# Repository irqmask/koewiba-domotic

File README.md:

# koewiba-domotic
home-automation

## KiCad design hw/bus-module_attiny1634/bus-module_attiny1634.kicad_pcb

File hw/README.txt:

To load KICAD symbols and footprints, make a symbolic link called 'kicadlibrary' to your checked-out symbol- and footprint- library.
e.g. ln -s ~/Projekte/electronic/00library/kicad/ kicadlibrary

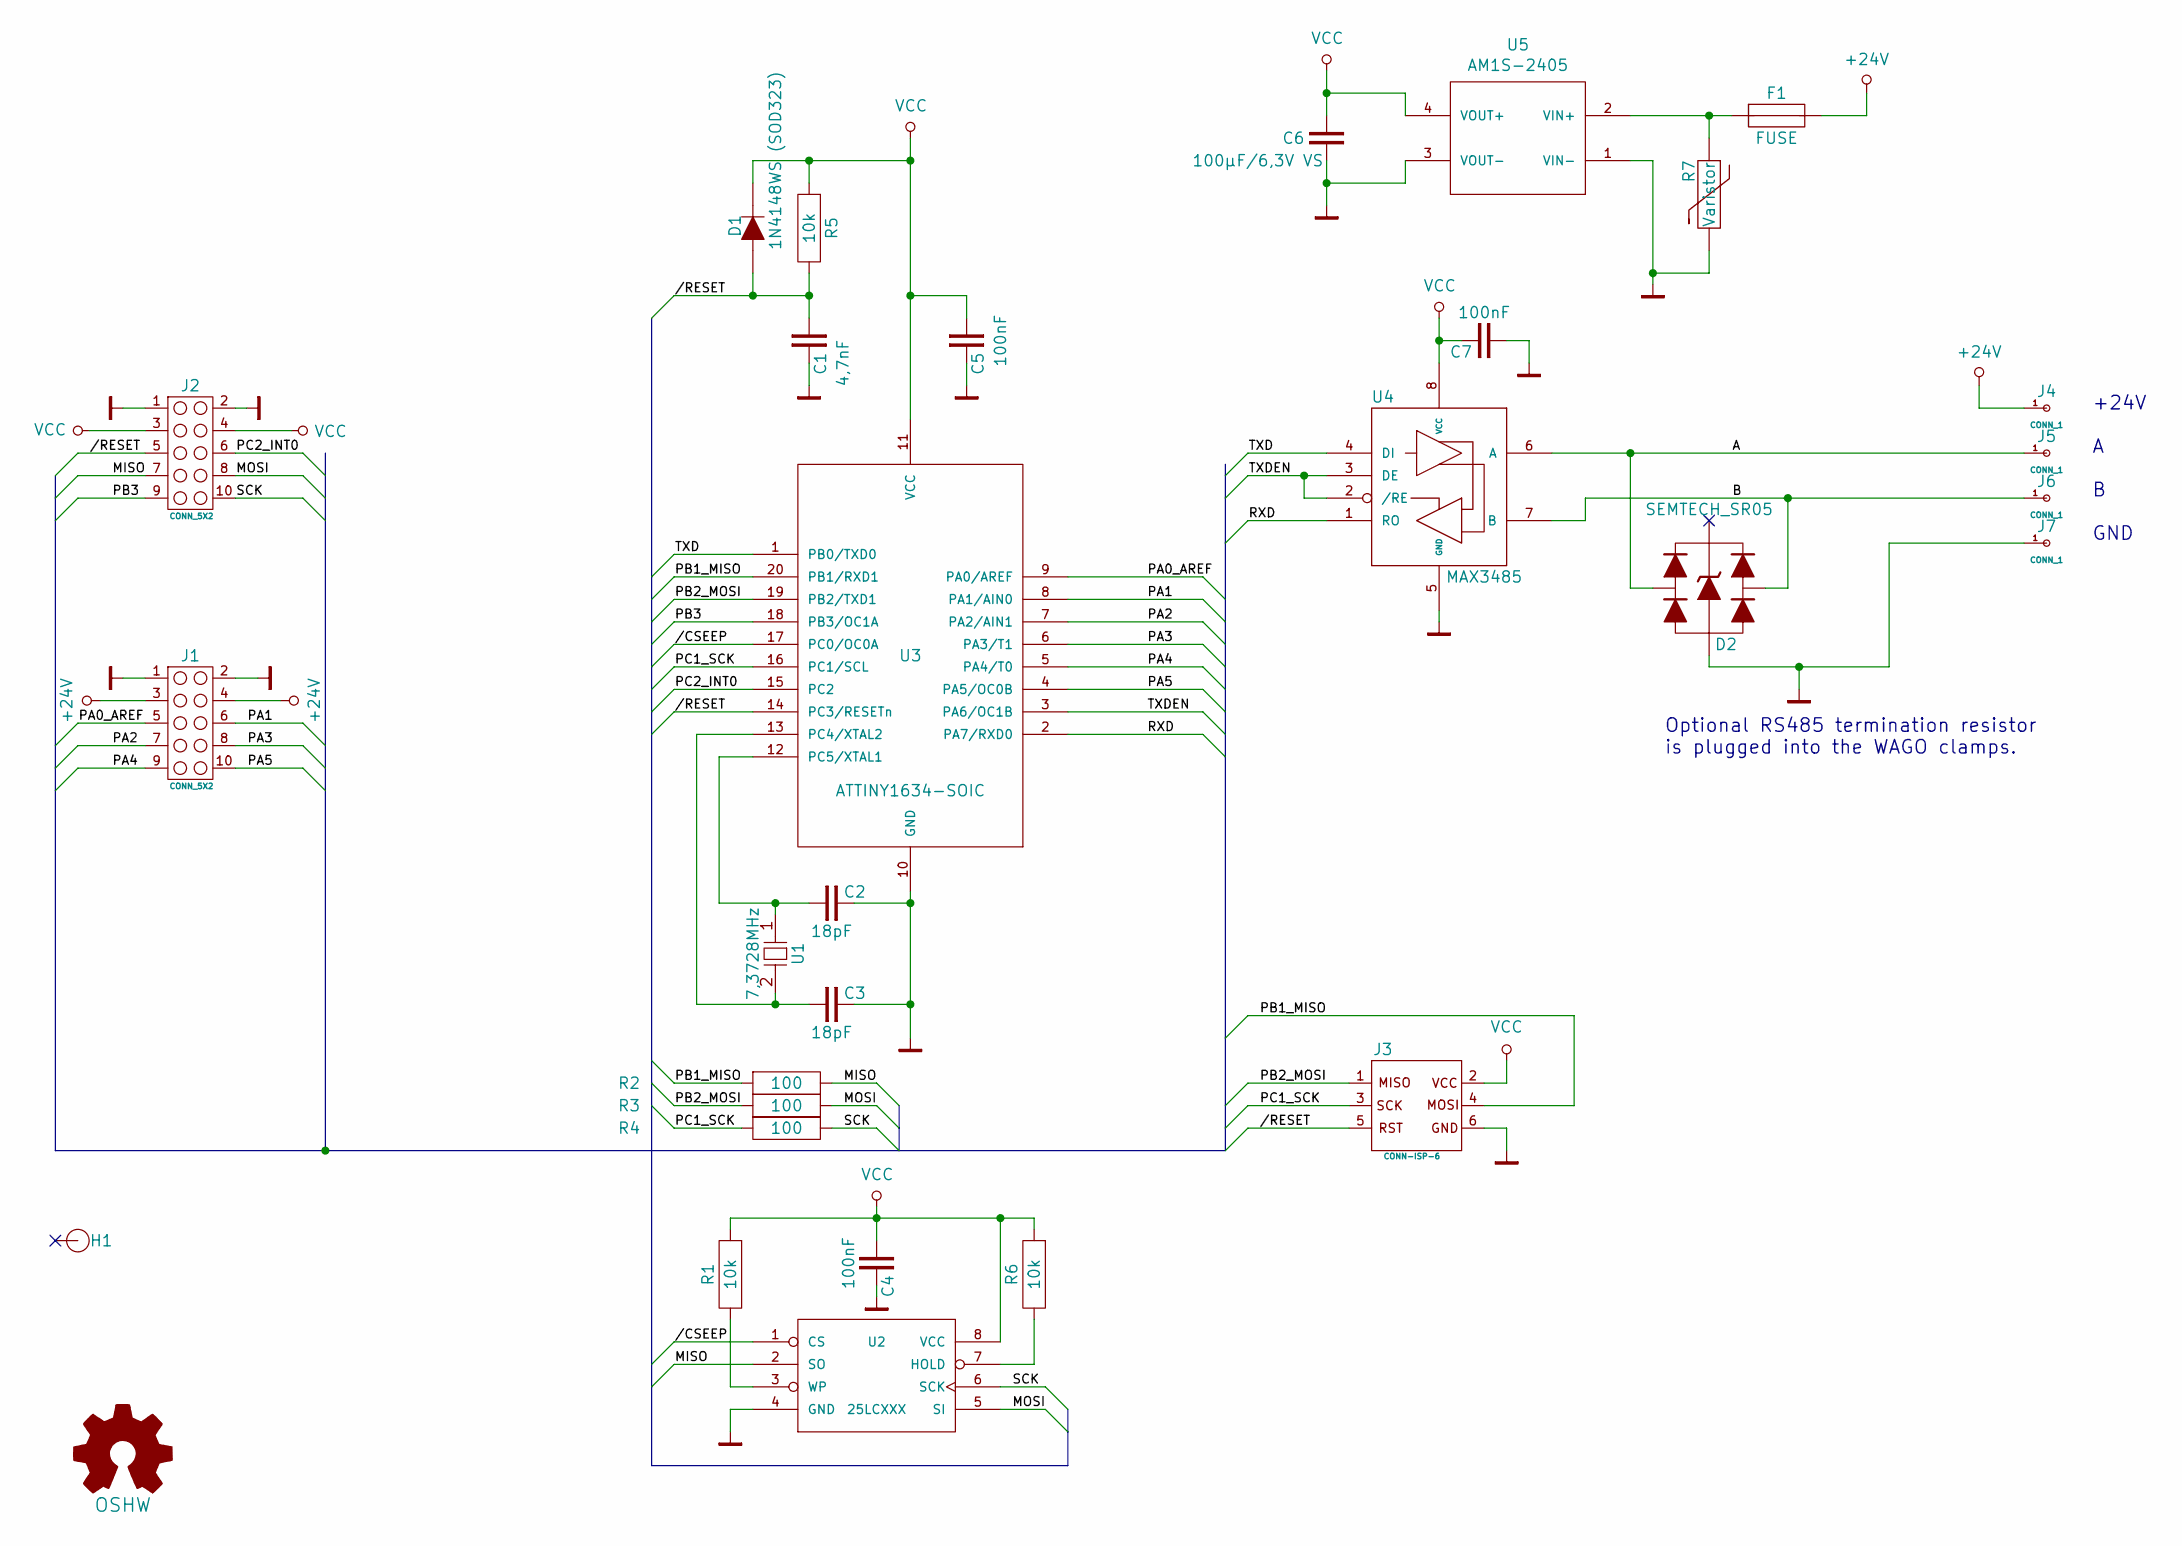
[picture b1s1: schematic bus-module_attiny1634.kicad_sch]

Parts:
C1: 4,7nF; C_0805
C2, C3: 18pF; C_0805
C4, C5, C7: 100nF; C_0805
C6: 100µF/6,3V VS; C_1206
D1: 1N4148WS (SOD323); D_SOD323
D2: SEMTECH_SR05; D_SOT143
F1: FUSE; R_1206
H1: HOLE; HOLE_2.5mm
J1, J2: CONN_5X2; HEADER_5x2
J3: CONN-ISP-6; HEADER_3x2
J4, J5, J6, J7: CONN_1; WAGO243
LOGO1: OSHW; Symbol_OSHW-Logo_SilkScreen
R1, R5, R6: 10k; R_0805
R2, R3, R4: 100; R_0805
R7: Varistor; R400
U1: 7,3728MHz; CRY_HC49_SMD
U2: 25LCXXX; SO8E
U3: ATTINY1634-SOIC; SO20L
U4: MAX3485; SO8E
U5: AM1S-2405; AM1S-XXXX_SIL4

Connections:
+24V: F1.2, J1.3, J1.4, J4.1
//CSEEP: U2.1 (CS), U3.17 (PC0/OC0A)
//RESET: C1.1, D1.1 (A), J2.5, J3.5, R5.2, U3.14 (PC3/RESETn)
/A: D2.4, J5.1, U4.6 (A)
/B: D2.3, J6.1, U4.7 (B)
/MISO: J2.7, R2.2, U2.2 (SO)
/MOSI: J2.8, R3.2, U2.5 (SI)
/PA0_AREF: J1.5, U3.9 (PA0/AREF)
/PA1: J1.6, U3.8 (PA1/AIN0)
/PA2: J1.7, U3.7 (PA2/AIN1)
/PA3: J1.8, U3.6 (PA3/T1)
/PA4: J1.9, U3.5 (PA4/T0)
/PA5: J1.10, U3.4 (PA5/OC0B)
/PB1_MISO: J3.4, R2.1, U3.20 (PB1/RXD1)
/PB2_MOSI: J3.1, R3.1, U3.19 (PB2/TXD1)
/PB3: J2.9, U3.18 (PB3/OC1A)
/PC1_SCK: J3.3, R4.1, U3.16 (PC1/SCL)
/PC2_INT0: J2.6, U3.15 (PC2)
/RXD: U3.2 (PA7/RXD0), U4.1 (RO)
/SCK: J2.10, R4.2, U2.6 (SCK)
/TXD: U3.1 (PB0/TXD0), U4.4 (DI)
/TXDEN: U3.3 (PA6/OC1B), U4.2 (/RE), U4.3 (DE)
GND: C1.2, C2.2, C3.2, C4.2, C5.2, C6.2, C7.1, D2.1, J1.1, J1.2, J2.1, J2.2, J3.6, J7.1, R7.2, U2.4 (GND), U3.10 (GND), U4.5 (GND), U5.1 (VIN-), U5.3 (VOUT-)
unnamed: C2.1, U1.1, U3.12 (PC5/XTAL1)
unnamed: C3.1, U1.2, U3.13 (PC4/XTAL2)
unnamed: F1.1, R7.1, U5.2 (VIN+)
unnamed: R1.2, U2.3 (WP)
unnamed: R6.2, U2.7 (HOLD)
VCC: C4.1, C5.1, C6.1, C7.2, D1.2 (C), J2.3, J2.4, J3.2, R1.1, R5.1, R6.1, U2.8 (VCC), U3.11 (VCC), U4.8 (VCC), U5.4 (VOUT+)

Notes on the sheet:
+24V A B GND
Optional RS485 termination resistor is plugged into the WAGO clamps.

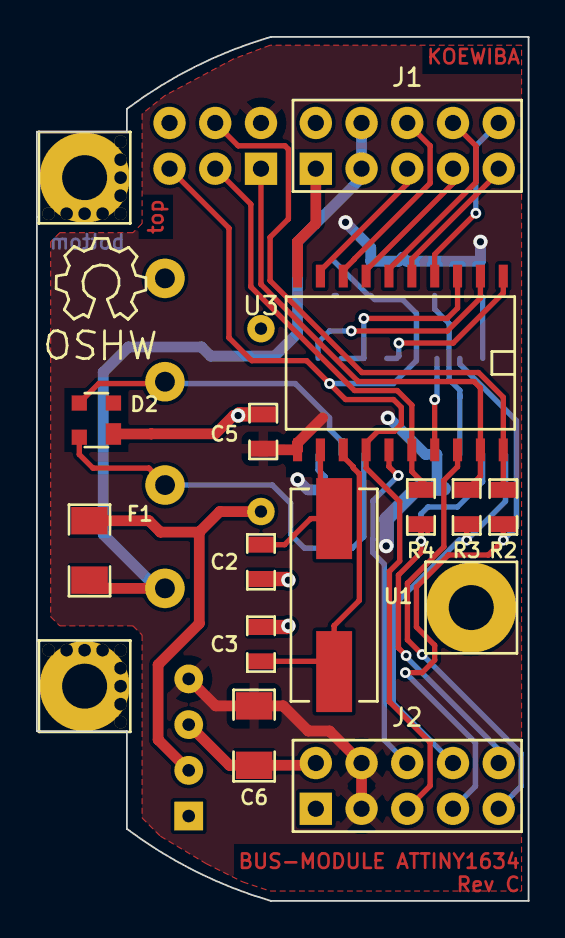
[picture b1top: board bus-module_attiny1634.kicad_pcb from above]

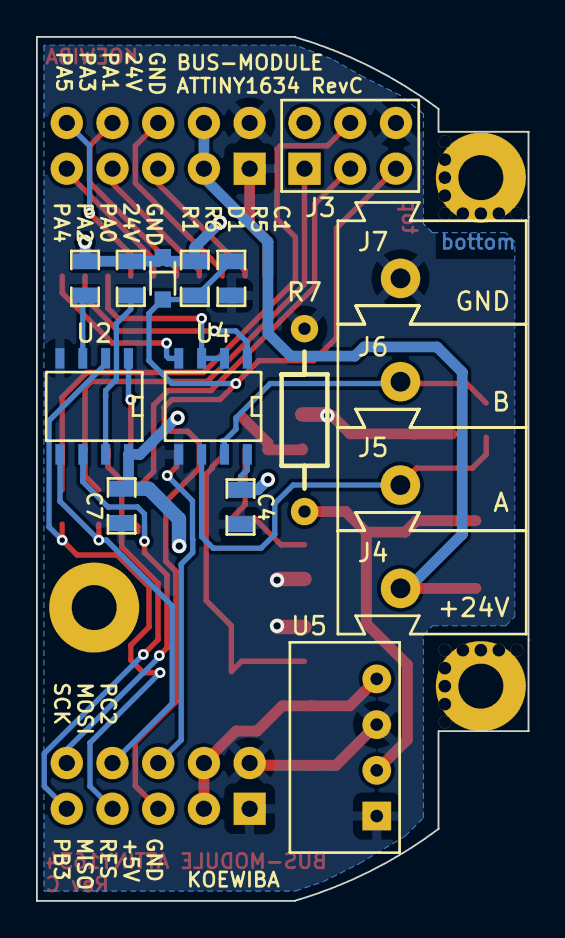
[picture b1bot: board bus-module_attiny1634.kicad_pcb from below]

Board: 2 copper layers, 27.3 x 48.0 mm, 33 parts (16 on the bottom side), 29 nets.

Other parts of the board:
HOLE_2.5mm, HOLE_2.5mm#2: VAL**; HOLE_2.5mm

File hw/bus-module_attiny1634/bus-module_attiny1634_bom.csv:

Id,Quantity,Designator,Package,Designation
9,1,C1,C_0805,"4,7nF"
10,2,"C2,C3",C_0805,18pF
6,3,"C5,C7,C4",C_0805,100nF
22,1,C6,C_1206,"100µF/6,3V VS"
7,1,D1,D_SOD323,1N4148WS (SOD323)
3,1,D2,D_SOT143,SEMTECH_SR05
23,1,F1,R_1206,FUSE
14,1,H1,HOLE_2.5mm,HOLE
11,2,"HOLE_2.5mm,HOLE_2.5mm",HOLE_2.5mm,VAL**
15,2,"J2,J1",HEADER_5x2,CONN_5X2
13,1,J3,HEADER_3x2,CONN-ISP-6
1,4,"J6,J5,J4,J7",WAGO243,CONN_1
12,1,LOGO1,Symbol_OSHW-Logo_SilkScreen,OSHW
5,3,"R2,R3,R4",R_0805,100
8,3,"R5,R6,R1",R_0805,10k
21,1,R7,R400,Varistor
19,2,"REF**,REF**",Perforation_5mm,Perforation_5mm
20,2,"REF**,REF**",Perforation_4mm,Perforation_4mm
4,1,U1,CRY_HC49_SMD,"7,3728MHz"
18,1,U2,SO8E,25LCXXX
2,1,U3,SO20L,ATTINY1634-SOIC
16,1,U4,SO8E,MAX3485
17,1,U5,AM1S-XXXX_SIL4,AM1S-2405

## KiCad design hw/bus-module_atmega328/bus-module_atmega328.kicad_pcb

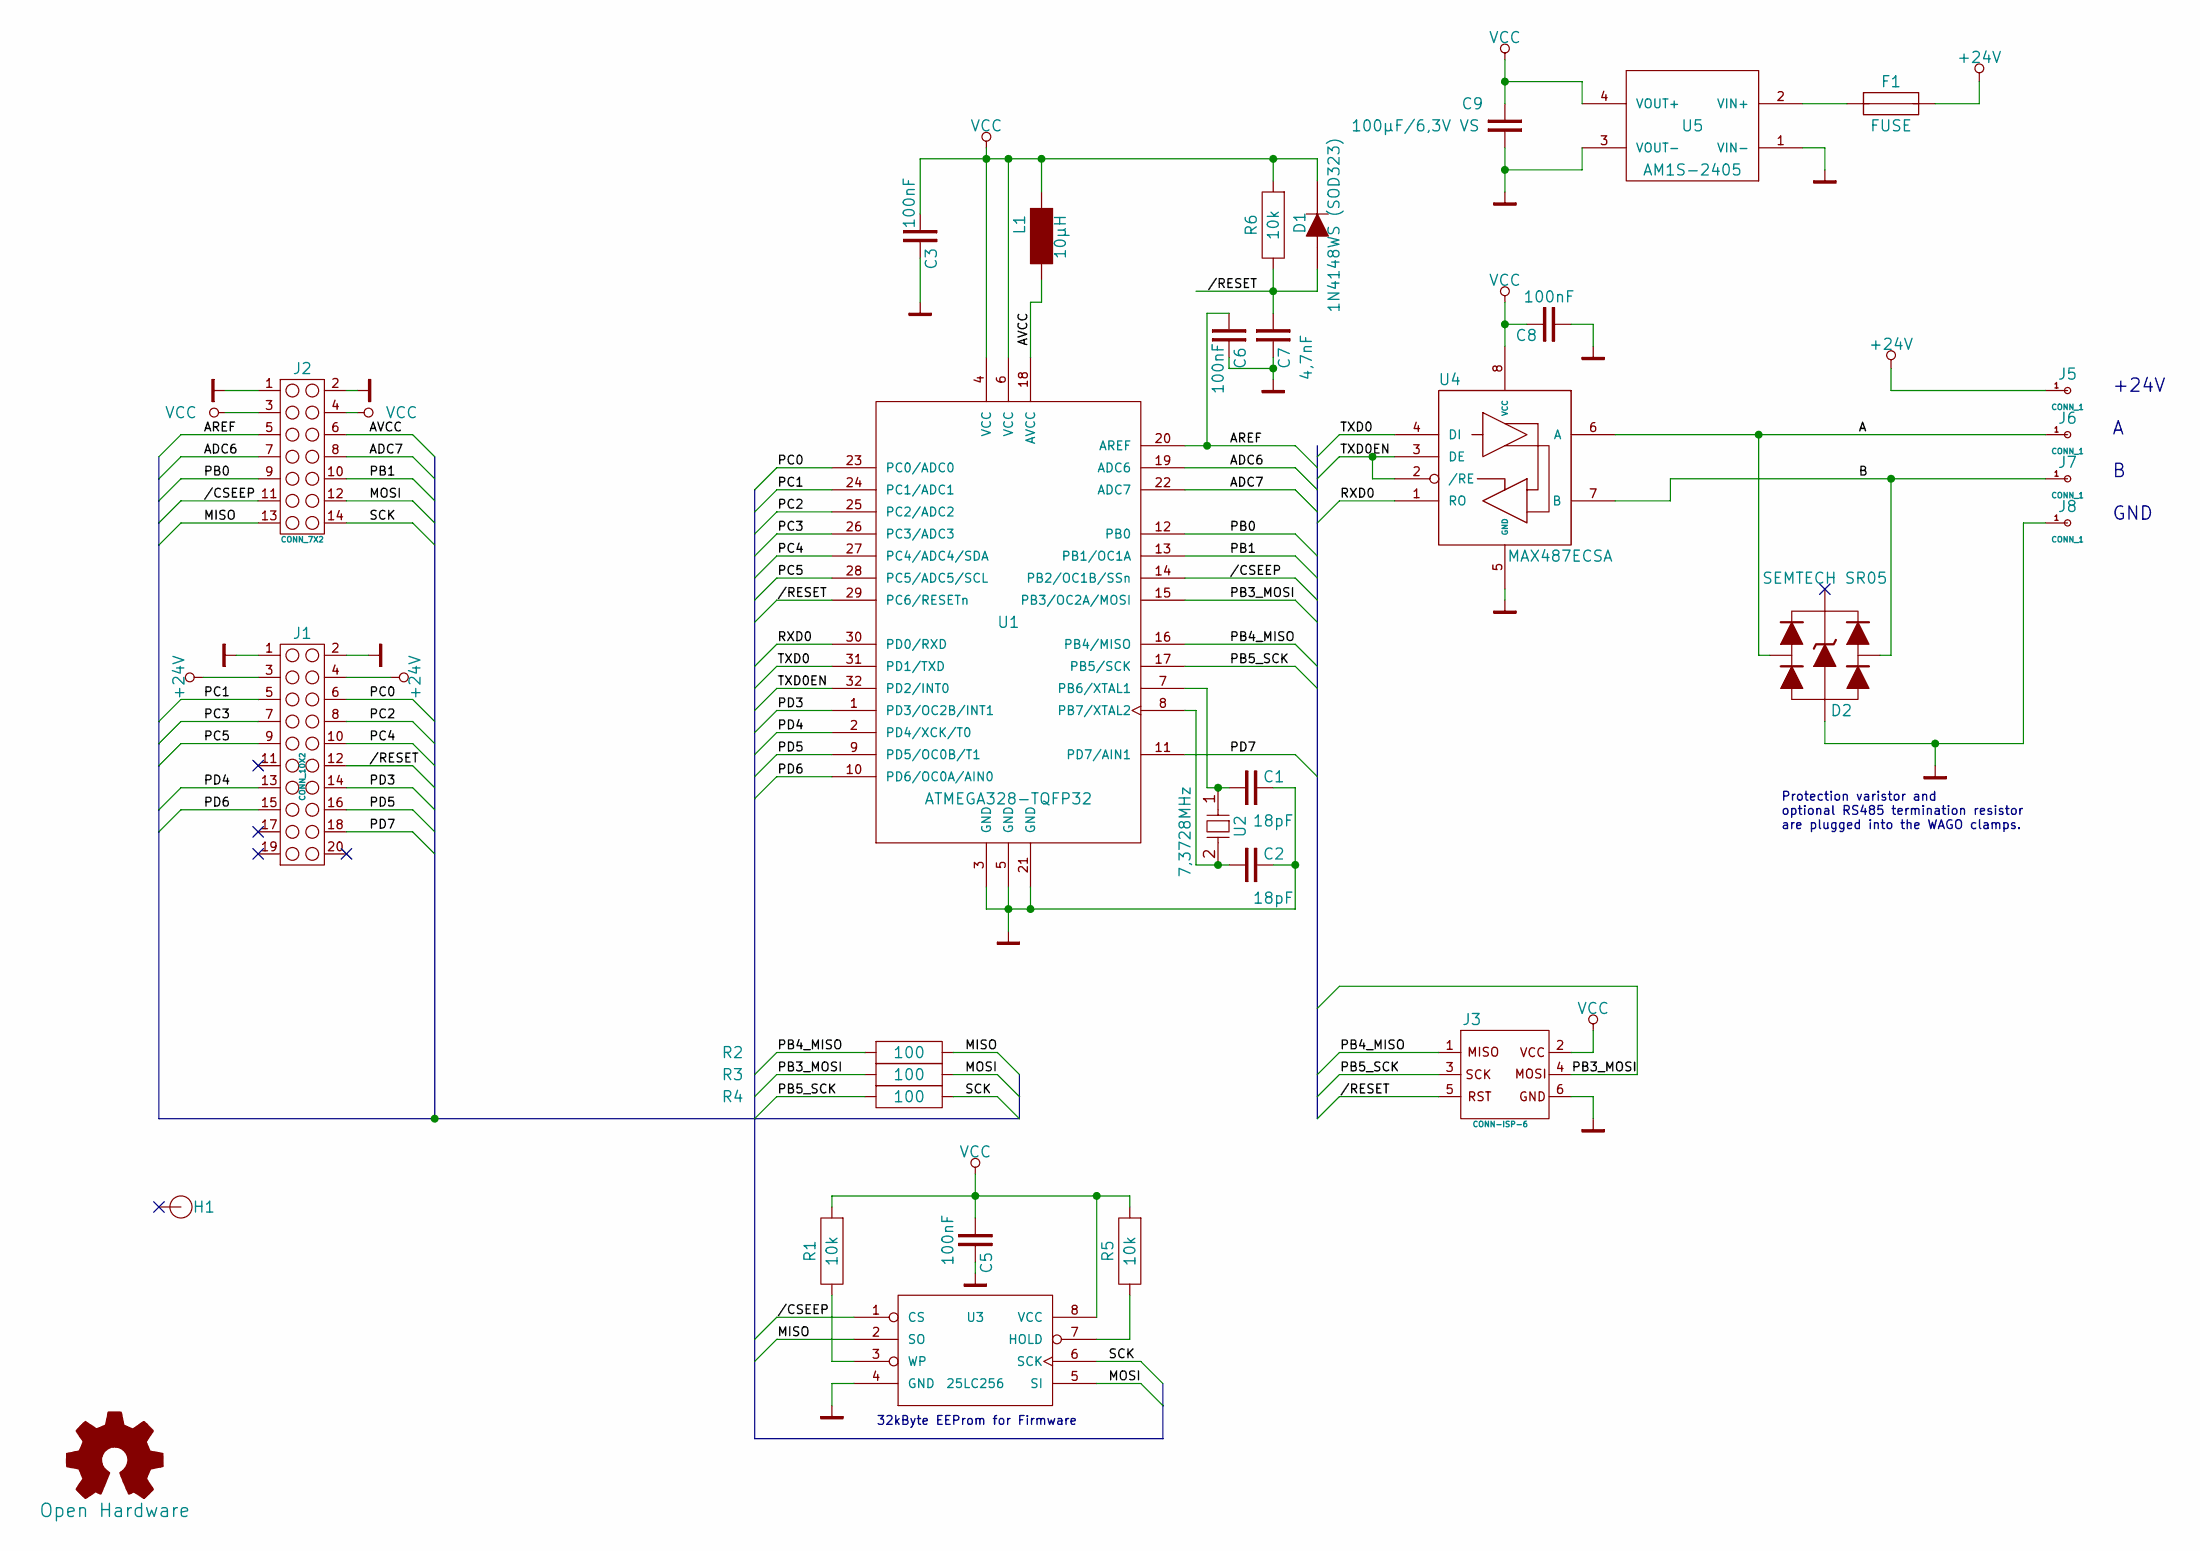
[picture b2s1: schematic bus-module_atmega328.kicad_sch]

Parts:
C1, C2: 18pF; C_0805
C3, C5, C6, C8: 100nF; C_0805
C7: 4,7nF; C_0805
C9: 100µF/6,3V VS; C_1206
D1: 1N4148WS (SOD323); D_SOD323
D2: SEMTECH SR05; D_SOT143
F1: FUSE; R_1812
H1: HOLE; HOLE_2.5mm
J1: CONN_10X2; HEADER_10x2
J2: CONN_7X2; HEADER_7x2
J3: CONN-ISP-6; HEADER_3x2
J5, J6, J7, J8: CONN_1; WAGO243
L1: 10µH; L_0805
LOGO1: Open Hardware; Symbol_OSHW-Logo_SilkScreen
R1, R5, R6: 10k; R_0805
R2, R3, R4: 100; R_0805
U1: ATMEGA328-TQFP32; TQFP-32_7x7mm_Pitch0.8mm
U2: 7,3728MHz; CRY_HC49_SMD
U3: 25LC256; SO8E
U4: MAX487ECSA; SO8E
U5: AM1S-2405; AM1S-XXXX_SIL4

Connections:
+24V: F1.2, J1.3, J1.4, J5.1
//CSEEP: J2.11, U1.14 (PB2/OC1B/SSn), U3.1 (CS)
//RESET: C7.1, D1.1 (A), J1.12, J3.5, R6.2, U1.29 (PC6/RESETn)
/A: D2.4, J6.1, U4.6 (A)
/ADC6: J2.7, U1.19 (ADC6)
/ADC7: J2.8, U1.22 (ADC7)
/AREF: C6.1, J2.5, U1.20 (AREF)
/AVCC: J2.6, L1.2, U1.18 (AVCC)
/B: D2.3, J7.1, U4.7 (B)
/MISO: J2.13, R2.2, U3.2 (SO)
/MOSI: J2.12, R3.2, U3.5 (SI)
/PB0: J2.9, U1.12 (PB0)
/PB1: J2.10, U1.13 (PB1/OC1A)
/PB3_MOSI: J3.4, R3.1, U1.15 (PB3/OC2A/MOSI)
/PB4_MISO: J3.1, R2.1, U1.16 (PB4/MISO)
/PB5_SCK: J3.3, R4.1, U1.17 (PB5/SCK)
/PC0: J1.6, U1.23 (PC0/ADC0)
/PC1: J1.5, U1.24 (PC1/ADC1)
/PC2: J1.8, U1.25 (PC2/ADC2)
/PC3: J1.7, U1.26 (PC3/ADC3)
/PC4: J1.10, U1.27 (PC4/ADC4/SDA)
/PC5: J1.9, U1.28 (PC5/ADC5/SCL)
/PD3: J1.14, U1.1 (PD3/OC2B/INT1)
/PD4: J1.13, U1.2 (PD4/XCK/T0)
/PD5: J1.16, U1.9 (PD5/OC0B/T1)
/PD6: J1.15, U1.10 (PD6/OC0A/AIN0)
/PD7: J1.18, U1.11 (PD7/AIN1)
/RXD0: U1.30 (PD0/RXD), U4.1 (RO)
/SCK: J2.14, R4.2, U3.6 (SCK)
/TXD0: U1.31 (PD1/TXD), U4.4 (DI)
/TXD0EN: U1.32 (PD2/INT0), U4.2 (/RE), U4.3 (DE)
GND: C1.2, C2.2, C3.2, C5.2, C6.2, C7.2, C8.1, C9.2, D2.1, J1.1, J1.2, J2.1, J2.2, J3.6, J8.1, U1.3 (GND), U1.5 (GND), U1.21 (GND), U3.4 (GND), U4.5 (GND), U5.1 (VIN-), U5.3 (VOUT-)
unnamed: C1.1, U1.7 (PB6/XTAL1), U2.1
unnamed: C2.1, U1.8 (PB7/XTAL2), U2.2
unnamed: F1.1, U5.2 (VIN+)
unnamed: R1.2, U3.3 (WP)
unnamed: R5.2, U3.7 (HOLD)
VCC: C3.1, C5.1, C8.2, C9.1, D1.2 (C), J2.3, J2.4, J3.2, L1.1, R1.1, R5.1, R6.1, U1.4 (VCC), U1.6 (VCC), U3.8 (VCC), U4.8 (VCC), U5.4 (VOUT+)

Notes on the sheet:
Protection varistor and optional RS485 termination resistor are plugged into the WAGO clamps.
+24V A B GND
32kByte EEProm for Firmware

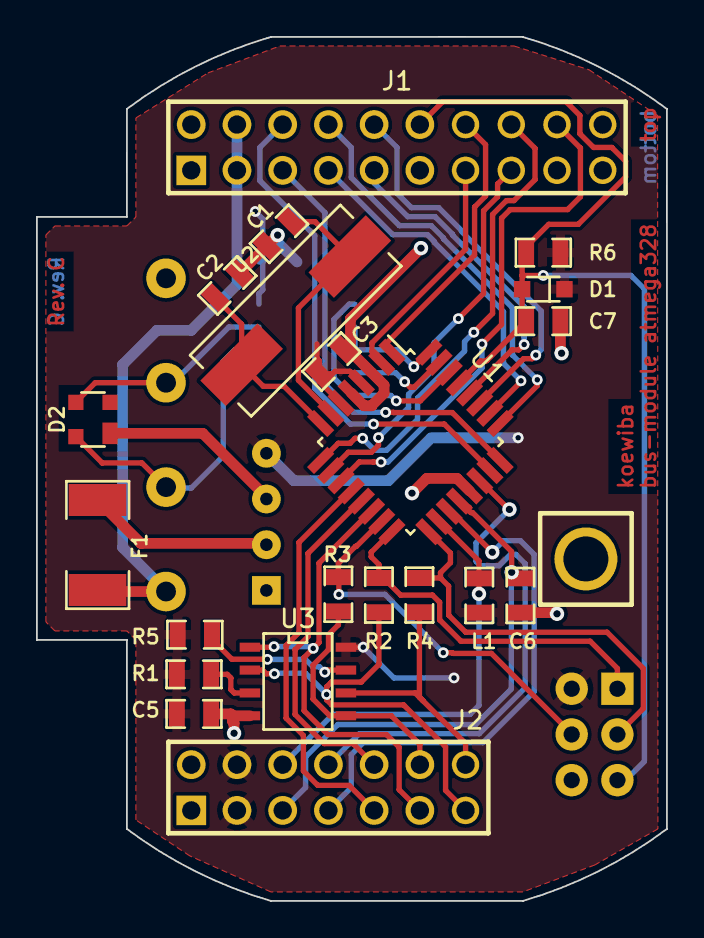
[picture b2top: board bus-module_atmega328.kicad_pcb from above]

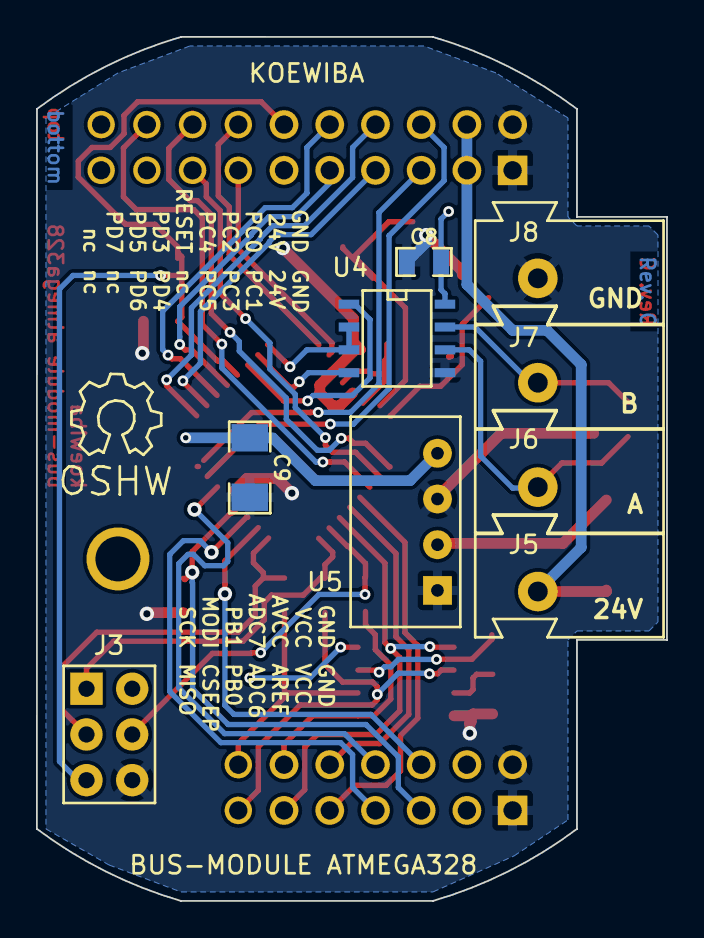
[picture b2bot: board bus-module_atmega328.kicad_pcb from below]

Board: 2 copper layers, 35.0 x 48.0 mm, 32 parts (10 on the bottom side), 38 nets.

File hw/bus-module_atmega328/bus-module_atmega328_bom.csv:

Id,Quantity,Designator,Package,Designation
5,2,"C2,C1",C_0805,18pF
3,4,"C3,C6,C5,C8",C_0805,100nF
4,1,C7,C_0805,"4,7nF"
21,1,C9,C_1206,"100µF/6,3V VS"
14,1,D1,D_SOD323,1N4148WS (SOD323)
16,1,D2,D_SOT143,SEMTECH SR05
15,1,F1,R_1812,FUSE
18,1,H1,HOLE_2.5mm,HOLE
12,1,J1,HEADER_10x2,CONN_10X2
20,1,J2,HEADER_7x2,CONN_7X2
9,1,J3,HEADER_3x2,CONN-ISP-6
2,4,"J6,J8,J7,J5",WAGO243,CONN_1
6,1,L1,L_0805,10µH
19,1,LOGO1,Symbol_OSHW-Logo_SilkScreen,Open Hardware
10,3,"R4,R2,R3",R_0805,100
13,3,"R6,R5,R1",R_0805,10k
1,1,U1,TQFP-32_7x7mm_Pitch0.8mm,ATMEGA328-TQFP32
17,1,U2,CRY_HC49_SMD,"7,3728MHz"
11,1,U3,SO8E,25LC256
7,1,U4,SO8E,MAX487ECSA
8,1,U5,AM1S-XXXX_SIL4,AM1S-2405

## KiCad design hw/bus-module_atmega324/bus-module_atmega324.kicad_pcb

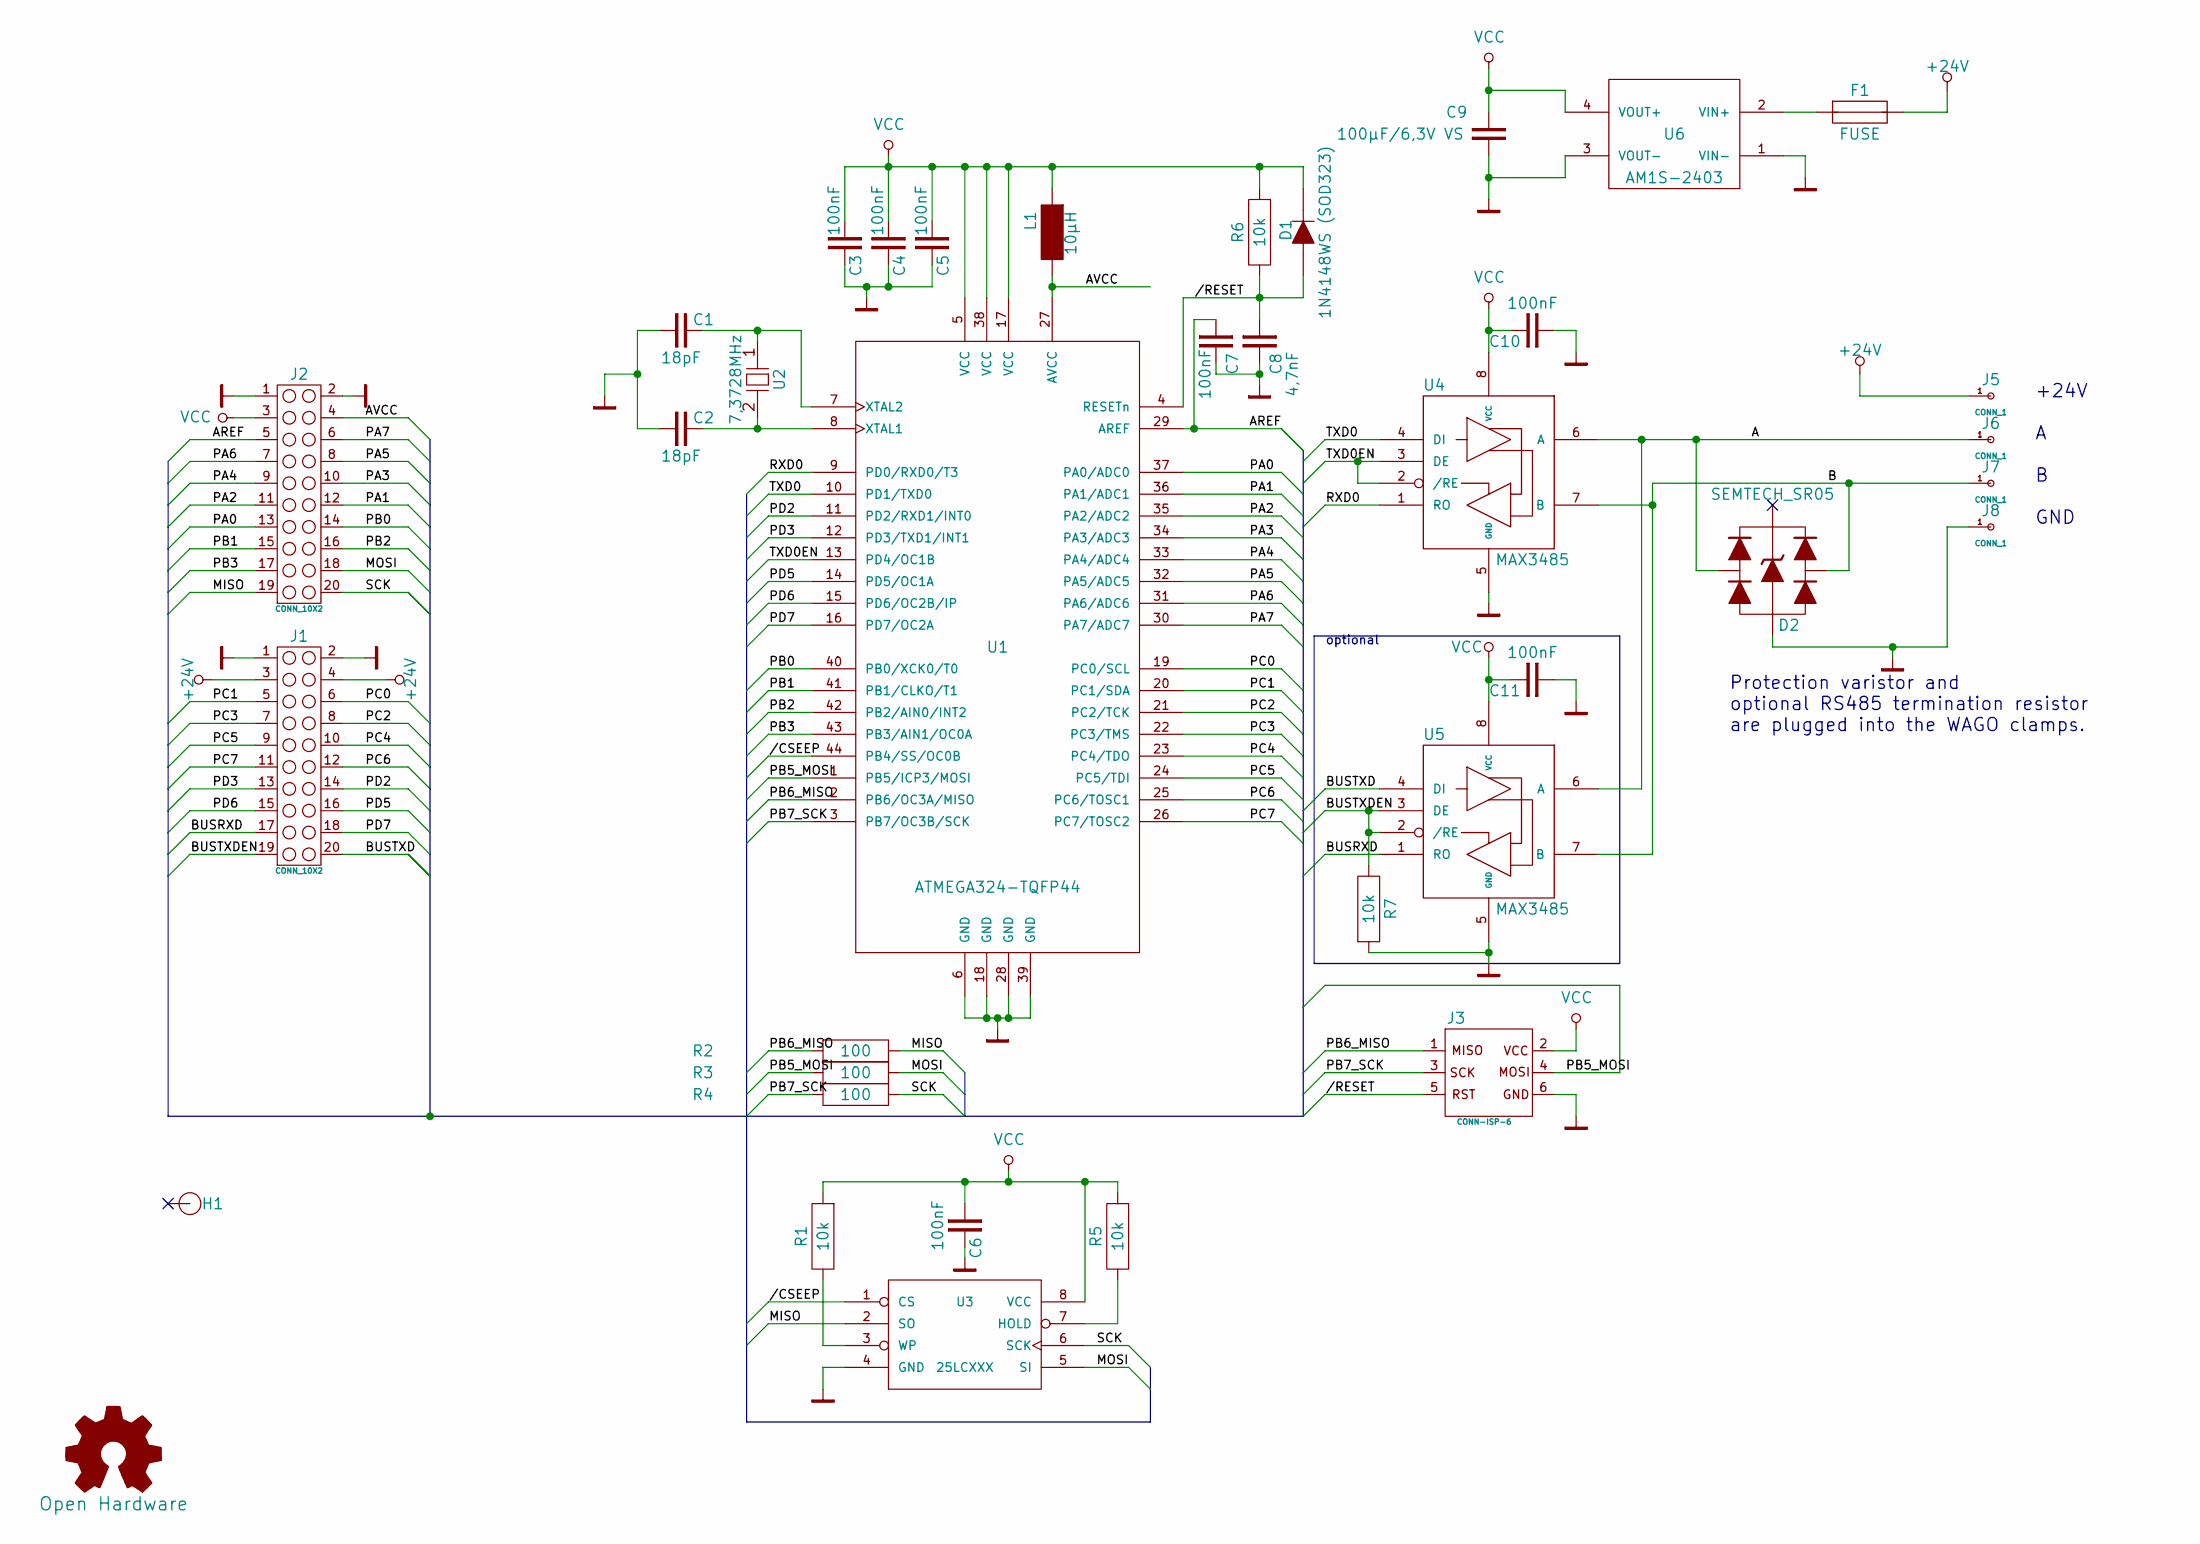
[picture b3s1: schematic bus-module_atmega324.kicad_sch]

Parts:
C1, C2: 18pF; C_0805
C3, C4, C5, C6, C7, C10, C11: 100nF; C_0805
C8: 4,7nF; C_0805
C9: 100µF/6,3V VS; C_1206
D1: 1N4148WS (SOD323); D_SOD323
D2: SEMTECH_SR05; D_SOT143
F1: FUSE; R_1812
H1: HOLE; HOLE_2.5mm
J1, J2: CONN_10X2; HEADER_10x2
J3: CONN-ISP-6; HEADER_3x2
J5, J6, J7, J8: CONN_1; WAGO243
L1: 10µH; L_0805
LOGO1: Open Hardware; Symbol_OSHW-Logo_SilkScreen
R1, R5, R6, R7: 10k; R_0805
R2, R3, R4: 100; R_0805
U1: ATMEGA324-TQFP44; TQFP-44_10x10mm_Pitch0.8mm
U2: 7,3728MHz; CRY_HC49_SMD
U3: 25LCXXX; SO8E
U4, U5: MAX3485; SO8E
U6: AM1S-2403; AM1S-XXXX_SIL4

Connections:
+24V: F1.2, J1.3, J1.4, J5.1
//CSEEP: U1.44 (PB4/SS/OC0B), U3.1 (CS)
//RESET: C8.1, D1.1 (A), J3.5, R6.2, U1.4 (RESETn)
/A: D2.4, J6.1, U4.6 (A), U5.6 (A)
/AREF: C7.1, J2.5, U1.29 (AREF)
/AVCC: J2.4, L1.2, U1.27 (AVCC)
/B: D2.3, J7.1, U4.7 (B), U5.7 (B)
/BUSRXD: J1.17, U5.1 (RO)
/BUSTXD: J1.20, U5.4 (DI)
/BUSTXDEN: J1.19, R7.2, U5.2 (/RE), U5.3 (DE)
/MISO: J2.19, R2.2, U3.2 (SO)
/MOSI: J2.18, R3.2, U3.5 (SI)
/PA0: J2.13, U1.37 (PA0/ADC0)
/PA1: J2.12, U1.36 (PA1/ADC1)
/PA2: J2.11, U1.35 (PA2/ADC2)
/PA3: J2.10, U1.34 (PA3/ADC3)
/PA4: J2.9, U1.33 (PA4/ADC4)
/PA5: J2.8, U1.32 (PA5/ADC5)
/PA6: J2.7, U1.31 (PA6/ADC6)
/PA7: J2.6, U1.30 (PA7/ADC7)
/PB0: J2.14, U1.40 (PB0/XCK0/T0)
/PB1: J2.15, U1.41 (PB1/CLKO/T1)
/PB2: J2.16, U1.42 (PB2/AIN0/INT2)
/PB3: J2.17, U1.43 (PB3/AIN1/OC0A)
/PB5_MOSI: J3.4, R3.1, U1.1 (PB5/ICP3/MOSI)
/PB6_MISO: J3.1, R2.1, U1.2 (PB6/OC3A/MISO)
/PB7_SCK: J3.3, R4.1, U1.3 (PB7/OC3B/SCK)
/PC0: J1.6, U1.19 (PC0/SCL)
/PC1: J1.5, U1.20 (PC1/SDA)
/PC2: J1.8, U1.21 (PC2/TCK)
/PC3: J1.7, U1.22 (PC3/TMS)
/PC4: J1.10, U1.23 (PC4/TDO)
/PC5: J1.9, U1.24 (PC5/TDI)
/PC6: J1.12, U1.25 (PC6/TOSC1)
/PC7: J1.11, U1.26 (PC7/TOSC2)
/PD2: J1.14, U1.11 (PD2/RXD1/INT0)
/PD3: J1.13, U1.12 (PD3/TXD1/INT1)
/PD5: J1.16, U1.14 (PD5/OC1A)
/PD6: J1.15, U1.15 (PD6/OC2B/IP)
/PD7: J1.18, U1.16 (PD7/OC2A)
/RXD0: U1.9 (PD0/RXD0/T3), U4.1 (RO)
/SCK: J2.20, R4.2, U3.6 (SCK)
/TXD0: U1.10 (PD1/TXD0), U4.4 (DI)
/TXD0EN: U1.13 (PD4/OC1B), U4.2 (/RE), U4.3 (DE)
GND: C1.1, C2.1, C3.2, C4.2, C5.2, C6.2, C7.2, C8.2, C9.2, C10.1, C11.1, D2.1, J1.1, J1.2, J2.1, J2.2, J3.6, J8.1, R7.1, U1.6 (GND), U1.18 (GND), U1.28 (GND), U1.39 (GND), U3.4 (GND), U4.5 (GND), U5.5 (GND), U6.1 (VIN-), U6.3 (VOUT-)
unnamed: C1.2, U1.7 (XTAL2), U2.1
unnamed: C2.2, U1.8 (XTAL1), U2.2
unnamed: F1.1, U6.2 (VIN+)
unnamed: R1.2, U3.3 (WP)
unnamed: R5.2, U3.7 (HOLD)
VCC: C3.1, C4.1, C5.1, C6.1, C9.1, C10.2, C11.2, D1.2 (C), J2.3, J3.2, L1.1, R1.1, R5.1, R6.1, U1.5 (VCC), U1.17 (VCC), U1.38 (VCC), U3.8 (VCC), U4.8 (VCC), U5.8 (VCC), U6.4 (VOUT+)

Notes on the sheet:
Protection varistor and optional RS485 termination resistor are plugged into the WAGO clamps.
optional
+24V A B GND

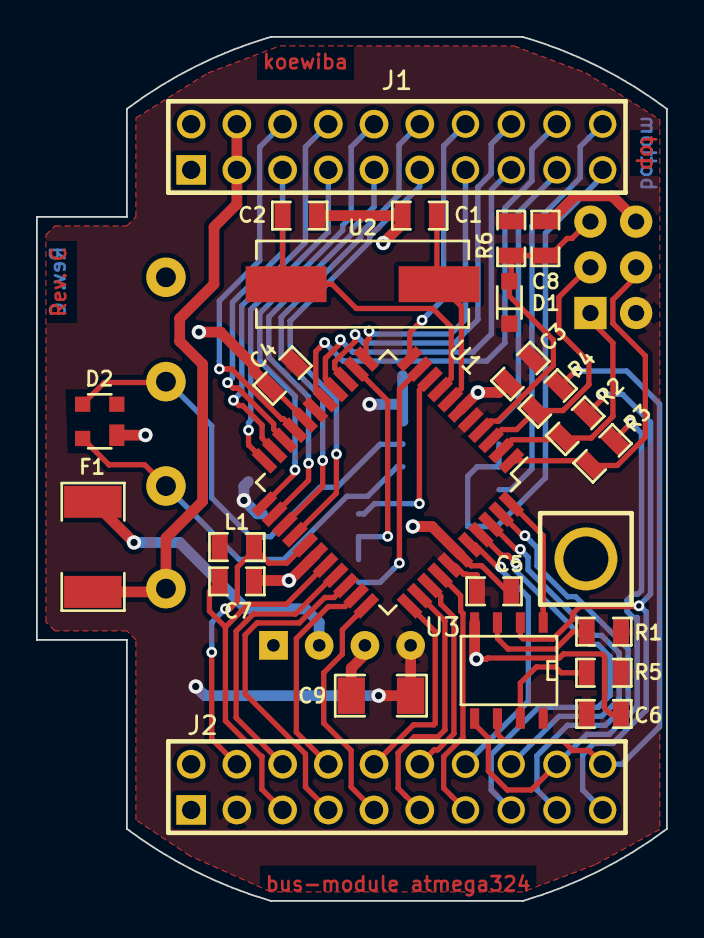
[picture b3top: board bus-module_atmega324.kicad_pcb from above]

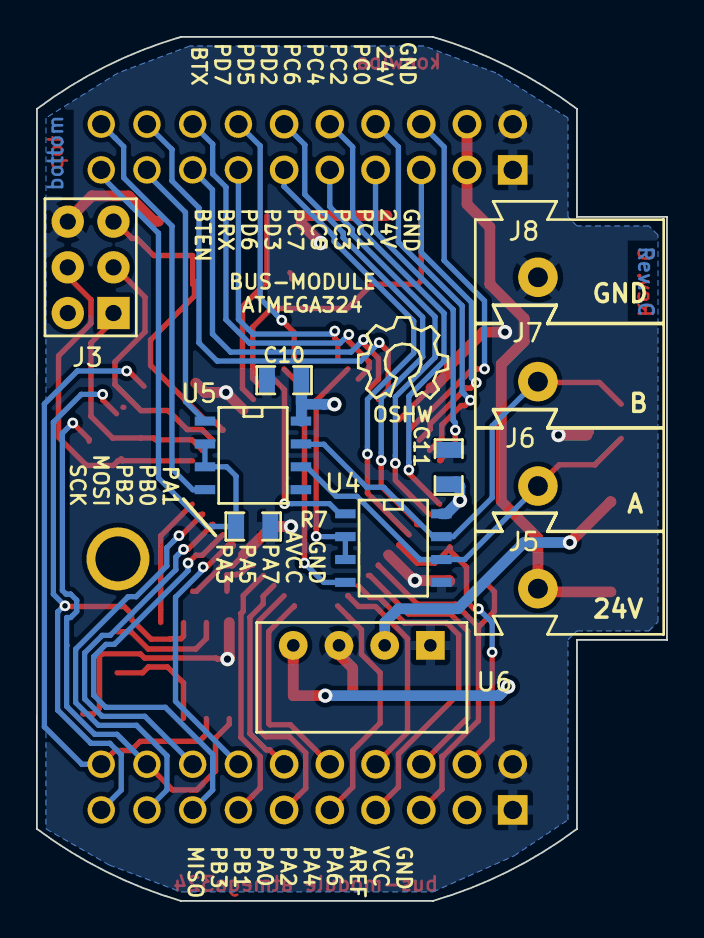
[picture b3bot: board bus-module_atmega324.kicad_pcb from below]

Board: 2 copper layers, 35.0 x 48.0 mm, 37 parts (12 on the bottom side), 51 nets.

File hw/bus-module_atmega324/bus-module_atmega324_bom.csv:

Id,Quantity,Designator,Package,Designation
16,2,"C2,C1",C_0805,18pF
12,7,"C3,C4,C5,C6,C7,C10,C11",C_0805,100nF
14,1,C8,C_0805,"4,7nF"
2,1,C9,C_1206,"100µF/6,3V VS"
13,1,D1,D_SOD323,1N4148WS (SOD323)
7,1,D2,D_SOT143,SEMTECH_SR05
8,1,F1,R_1812,FUSE
19,1,H1,HOLE_2.5mm,HOLE
18,2,"J1,J2",HEADER_10x2,CONN_10X2
4,1,J3,HEADER_3x2,CONN-ISP-6
3,4,"J8,J7,J6,J5",WAGO243,CONN_1
20,1,L1,L_0805,10µH
17,1,LOGO1,Symbol_OSHW-Logo_SilkScreen,Open Hardware
11,3,"R4,R2,R3",R_0805,100
10,4,"R6,R1,R5,R7",R_0805,10k
1,1,U1,TQFP-44_10x10mm_Pitch0.8mm,ATMEGA324-TQFP44
15,1,U2,CRY_HC49_SMD,"7,3728MHz"
5,1,U3,SO8E,25LCXXX
6,2,"U4,U5",SO8E,MAX3485
9,1,U6,AM1S-XXXX_SIL4,AM1S-2403

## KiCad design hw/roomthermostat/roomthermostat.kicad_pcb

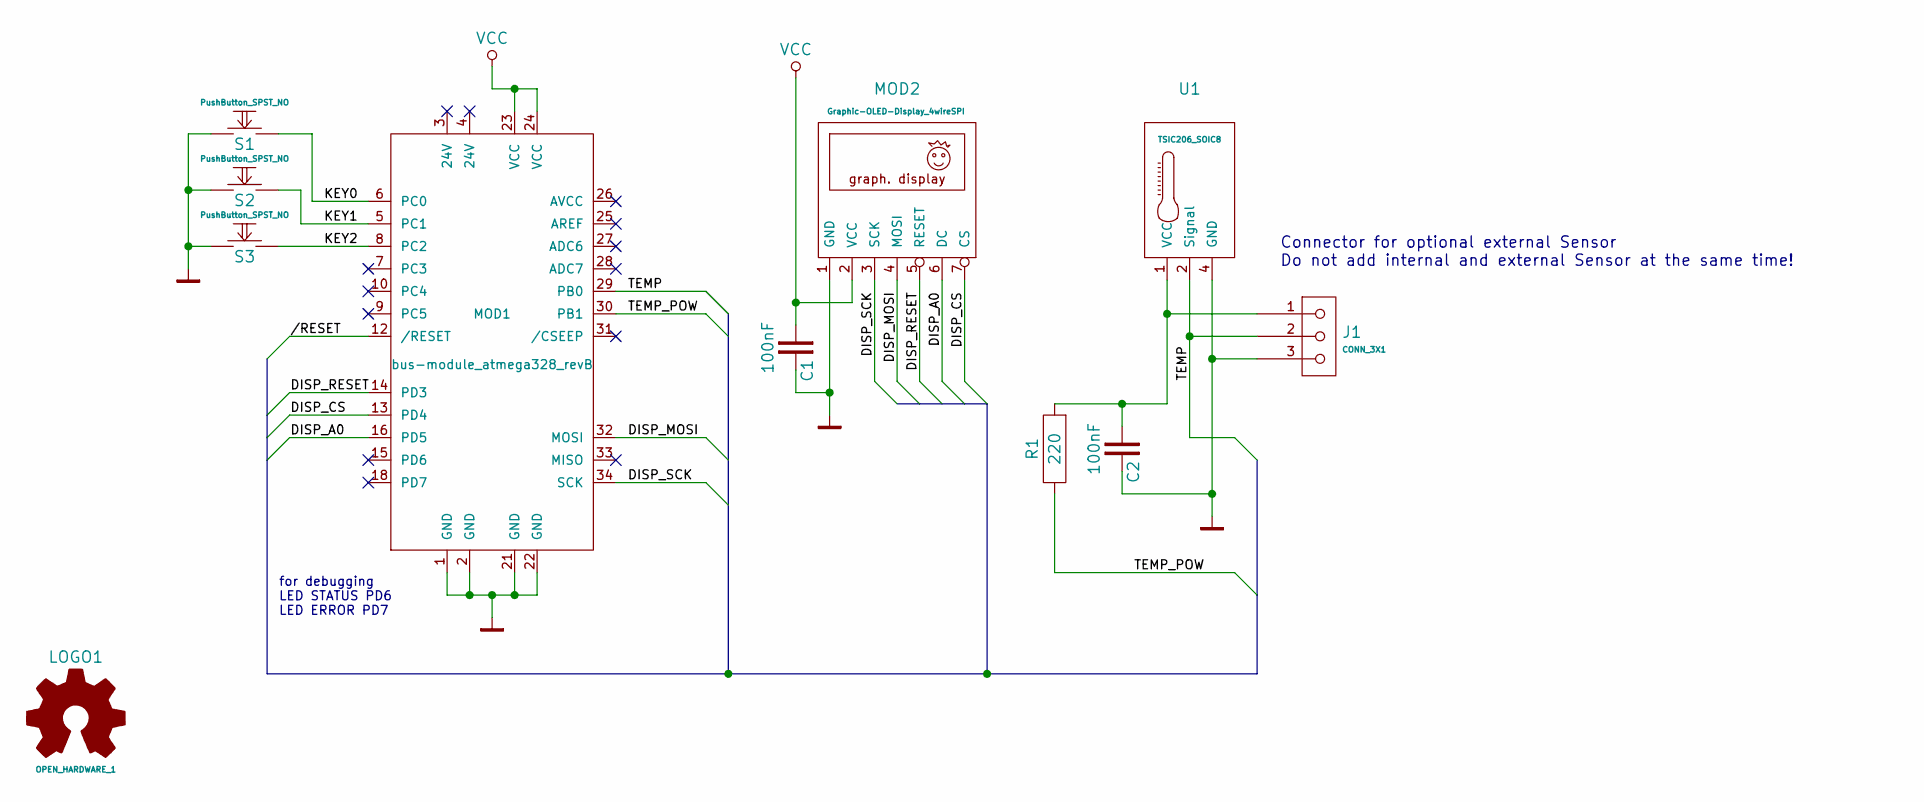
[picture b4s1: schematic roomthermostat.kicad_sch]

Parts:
C1, C2: 100nF; C_0805
J1: CONN_3X1; HEADER_3x1
LOGO1: OPEN_HARDWARE_1; Symbol_OSHW-Logo_Copper
MOD1: bus-module_atmega328_revB; bus-module_atmega328
MOD2: Graphic-OLED-Display_4wireSPI; GraphDisplay_1_OLED_27x27,5mm_030072BA
R1: 220; R_0805
S1, S2, S3: PushButton_SPST_NO; PushButton_SPST_SMD_JTP-1138_BacksideMount
U1: TSIC206_SOIC8; SO8E

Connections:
/DISP_A0: MOD1.16 (PD5), MOD2.6 (DC)
/DISP_CS: MOD1.13 (PD4), MOD2.7 (CS)
/DISP_MOSI: MOD1.32 (MOSI), MOD2.4 (MOSI)
/DISP_RESET: MOD1.14 (PD3), MOD2.5 (RESET)
/DISP_SCK: MOD1.34 (SCK), MOD2.3 (SCK)
/KEY0: MOD1.6 (PC0), S1.2
/KEY1: MOD1.5 (PC1), S2.2
/KEY2: MOD1.8 (PC2), S3.2
/TEMP: J1.2, MOD1.29 (PB0), U1.2 (Signal)
/TEMP_POW: MOD1.30 (PB1), R1.2
//RESET: MOD1.12 (/RESET)
GND: C1.2, C2.2, J1.3, MOD1.1 (GND), MOD1.2 (GND), MOD1.21 (GND), MOD1.22 (GND), MOD2.1 (GND), S1.1, S2.1, S3.1, U1.4 (GND)
unnamed: C2.1, J1.1, R1.1, U1.1 (VCC)
VCC: C1.1, MOD1.23 (VCC), MOD1.24 (VCC), MOD2.2 (VCC)

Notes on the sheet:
for debugging LED STATUS PD6 LED ERROR PD7
Connector for optional external Sensor Do not add internal and external Sensor at the same time!
